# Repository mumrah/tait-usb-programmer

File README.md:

# Tait TM8100 USB programming module

This board is bespoke USB to UART converter for programming Tait TM8100 series radios. It connects to the front
end of a radio using a DB9 connector and provides a sturdy USB-B connector for interfacing with a PC. The board
uses the MCP2200 chip from Microchip.

The current version is [v2](https://github.com/mumrah/tait-usb-programmer/tree/main/v2)

## Usage

To use the programmer, two pieces of software are required:

1) MCP2200 Windows Driver https://ww1.microchip.com/downloads/en/DeviceDoc/MCP2221_Windows_Driver_2021-02-22.zip
2) Tait TM8100 Programming Software (can be found in the [TARPN Tait documentation](http://tarpn.net/t/builder/tait_tm8105_notes/builders_radios_tait8105.html)).

If the MCP2200 driver link is dead, check the product page for a new link https://www.microchip.com/en-us/product/MCP2200 
and [file an issue](https://github.com/mumrah/tait-usb-programmer/issues) against this repository.

The board is designed to plug directly into the front panel of a TM810x radio. A USB-B to USB-A cable (such as a modern
printer cable) is then used to connect the programmer board into a PC. 

Once the board is plugged in and detected by Windows, check the Device Manager to determine which COM port
the programmer was registered as.

In the Tait software, under Tools -> Options, select the COM port that was found in the Device Manager

At this point, you can either "Read the Radio" or "Interrogate the Radio" using the Tait software. Refer to the 
[TARPN Tait documentation](http://tarpn.net/t/builder/tait_tm8105_notes/builders_radios_tait8105.html) for more details
on programming specifics.

## Programming the Programmer

This section only applies if you are building your own programmer. Once assembled, the board must be configured using 
the [software from Microchip](https://www.microchip.com/en-us/product/MCP2200). This is needed to invert the UART rx/tx 
signal levels as required by the Tait radios. With newer versions of the board (v2 and later), LEDs can be enabled by 
selecting "Enable Tx/Rx LEDs"

## Action Shot

Here is a video of a v2 board reading from a Tait TM8105

https://user-images.githubusercontent.com/55116/129118886-56906c2b-b291-4ea8-aef9-7abf3eee217b.mov

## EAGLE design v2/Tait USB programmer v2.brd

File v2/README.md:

# Aug 2021, v2

[OSHPark link](https://oshpark.com/shared_projects/BDVREM16)

Redesign of the board to use SSOP package and add two indicator LEDs. 

# BOM

Digi-Key part numbers.

* MCP2200 SSOP package, MCP2200-I/SS-ND
* DB9 socket, 609-5189-ND
* USB-B socket, UE27BC54130-ND
* C1, C4: 0.1µF ceramic capacitor, 56-1C10Z5U104M050B-ND
* Y1: 12MHz quartz crystal oscillator, 300-6027-ND
* C2, C3: 18-22pF ceramic capacitor, BC1004CT-ND
* R1: Any low value 1/8W resistor or a jumper wire
* R2: 10kΩ 1/8W resistor
* R3, R4: 1kΩ 1/8W resistor
* RX, TX: any suitable 3mm or 5mm LED

# Images

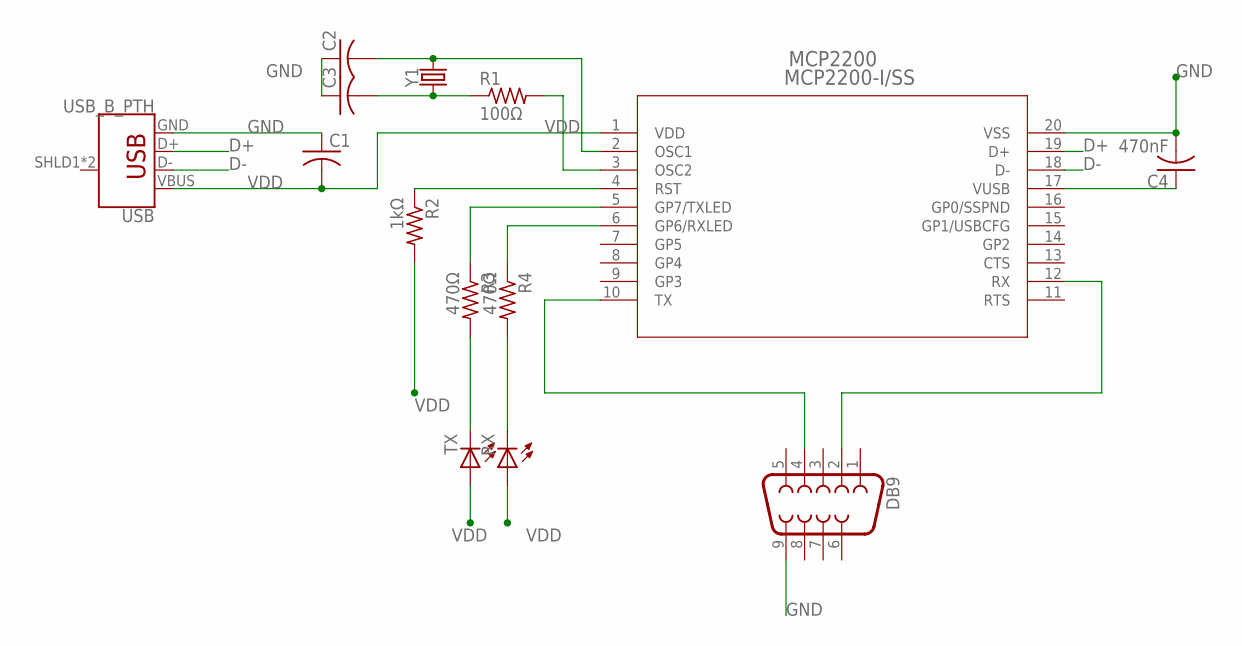
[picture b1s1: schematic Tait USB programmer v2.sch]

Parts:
C1: 0.1uF; C025-025X050
C2, C3: 22pF; C025-025X050
C4: 470nF; C025-025X050
DB9: DB9FEMALE; DB9
MCP2200: MCP2200-I/SS; SSOP20_MC_MCH
R1: 100Ω; 0204/7
R2: 1kΩ; 0204/7
R3, R4: 470Ω; 0204/7
RX: LED3MM
TX: LED3MM
USB: USB_B_PTH; USB-B-PTH
Y1: 12MHz; HC49U

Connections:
D+: MCP2200.19 (D+), USB.D+
D-: MCP2200.18 (D-), USB.D-
GND: C1.1, C2.1, C3.1, C4.2, DB9.9, MCP2200.20 (VSS), USB.GND
unnamed: C3.2, R1.1, Y1.1
unnamed: MCP2200.4 (RST), R2.1
unnamed: R3.2, TX.K (C)
unnamed: C2.2, MCP2200.2 (OSC1), Y1.2
unnamed: C4.1, MCP2200.17 (VUSB)
unnamed: DB9.2, MCP2200.12 (RX)
unnamed: DB9.4, MCP2200.10 (TX)
unnamed: R4.2, RX.K (C)
unnamed: MCP2200.6 (GP6/RXLED), R4.1
unnamed: MCP2200.3 (OSC2), R1.2
unnamed: MCP2200.5 (GP7/TXLED), R3.1
VDD: C1.2, MCP2200.1 (VDD), R2.2, RX.A, TX.A, USB.VBUS

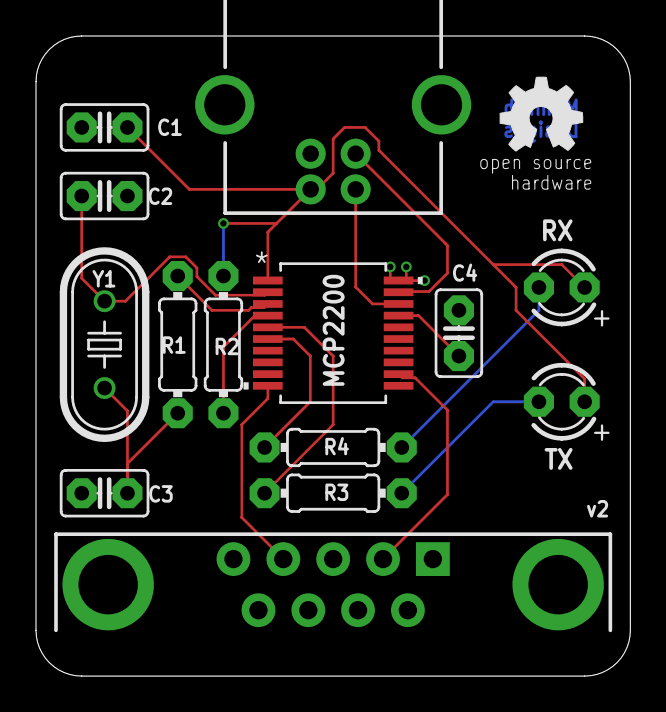
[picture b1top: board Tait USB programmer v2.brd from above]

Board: 2 copper layers, 33.0 x 35.6 mm, 15 parts (0 on the bottom side), 15 nets.

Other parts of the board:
U$1: OSHW_5MM

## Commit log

2021-07-30 Add CC-BY-SA license
2021-08-14 Adding EAGLE files for v2 board

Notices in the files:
parts and their libraries:
SparkFun-Connectors: Licensing: Creative Commons ShareAlike 4.0 International - https://creativecommons.org/licenses/by-sa/4.0
